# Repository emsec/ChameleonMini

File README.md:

Chameleon-Mini
==============
This is the official repository of ChameleonMini, a freely programmable, portable tool for NFC security analysis that can emulate and clone contactless cards, read RFID tags and sniff/log RF data. Thanks to over 1700 backers from our [Kickstarter project](https://www.kickstarter.com/projects/1980078555/chameleonmini-a-versatile-nfc-card-emulator-and-mo), the current Revision G has been realized by Kasper & Oswald GmbH.

The ChameleonMini RevG is now also available via the Kasper & Oswald [Webshop](https://shop.kasper.it/). Thank you for supporting the project!

IMPORTANT: Third-party Clones
------------------
We are aware of various third-party ChameleonMini clones or modified variants that are available on the Internet. Warning: We have evidence that some of these devices are defective or suffer from reading problems et cetera. Please understand that we cannot give support for these non-official devices, as we have no schematics / layout or other information, nor do we know the manufacturers. In case of problems, please contact the manufacturers of your device directly.

Note to the manufacturers: Some of the third-party ChameleonMini are violating the ChameleonMini license, please obey the license (see LICENSE.txt)!

First Steps
-----------
To upgrade the firmware of your ChameleonMini, please visit the [Getting Started page](https://cdn.statically.io/gh/emsec/ChameleonMini/master/Doc/Doxygen/html/Page_GettingStarted.html) from the [doxygen documentation](https://cdn.statically.io/gh/emsec/ChameleonMini/master/Doc/Doxygen/html/index.html).

Supported Cards and Codecs
--------------------------
See [here](https://github.com/emsec/ChameleonMini/wiki/Supported-Cards-and--Codecs). The linked wiki page also includes notes on DESFire emulation and certain cases of application specific emulation (Gallagher).

Questions
---------
If you have any questions, please visit the [Issues page](https://github.com/emsec/ChameleonMini/issues) and ask your questions there so everyone benefits from the answer.

**Please note that we cannot give any support if you have issues with the RevE-rebooted hardware or any GUI. Please use this issues page only for problems with the RevG hardware as distributed by Kasper & Oswald and for problems with the firmware from this page.** 

External Contributions
----------------------
We appreciate every contribution to the project. Have a look at the [External Contributions page](https://github.com/emsec/ChameleonMini/wiki/External-Contributions).

Repository Structure
--------------------
The code repository contains
* Doc: A doxygen documentation
* Drivers: Chameleon drivers for Windows and Linux
* Dumps: Dumps of different smartcards
* Hardware: The layout and schematics of the PCB
* Firmware: The complete firmware including a modified Atmel DFU bootloader and LUFA
* Software: Contains a python tool for an easy configuration (and more) of the ChameleonMini, Note that this is currently under construction
* RevE: Contains the whole contents of the discontinued RevE repository.
* RevE-light: Contains our development files for the RevE-light - **WARNING:** currently not supported / not functional

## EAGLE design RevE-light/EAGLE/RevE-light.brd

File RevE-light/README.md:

Chameleon-Mini RevE-light
==============

**WARNING:** The files in this folder are our current development version. *The hardware and software is not functional yet* - so do not use it. We will not answer any support inquiry regarding this version at the moment.

Structure
--------------------
This part of the code repository contains

* Hardware: The layout and schematics of the RevE-light - *NOT FUNCTIONAL*
* Firmware: The RevE-light firmware - *NOT FUNCTIONAL*

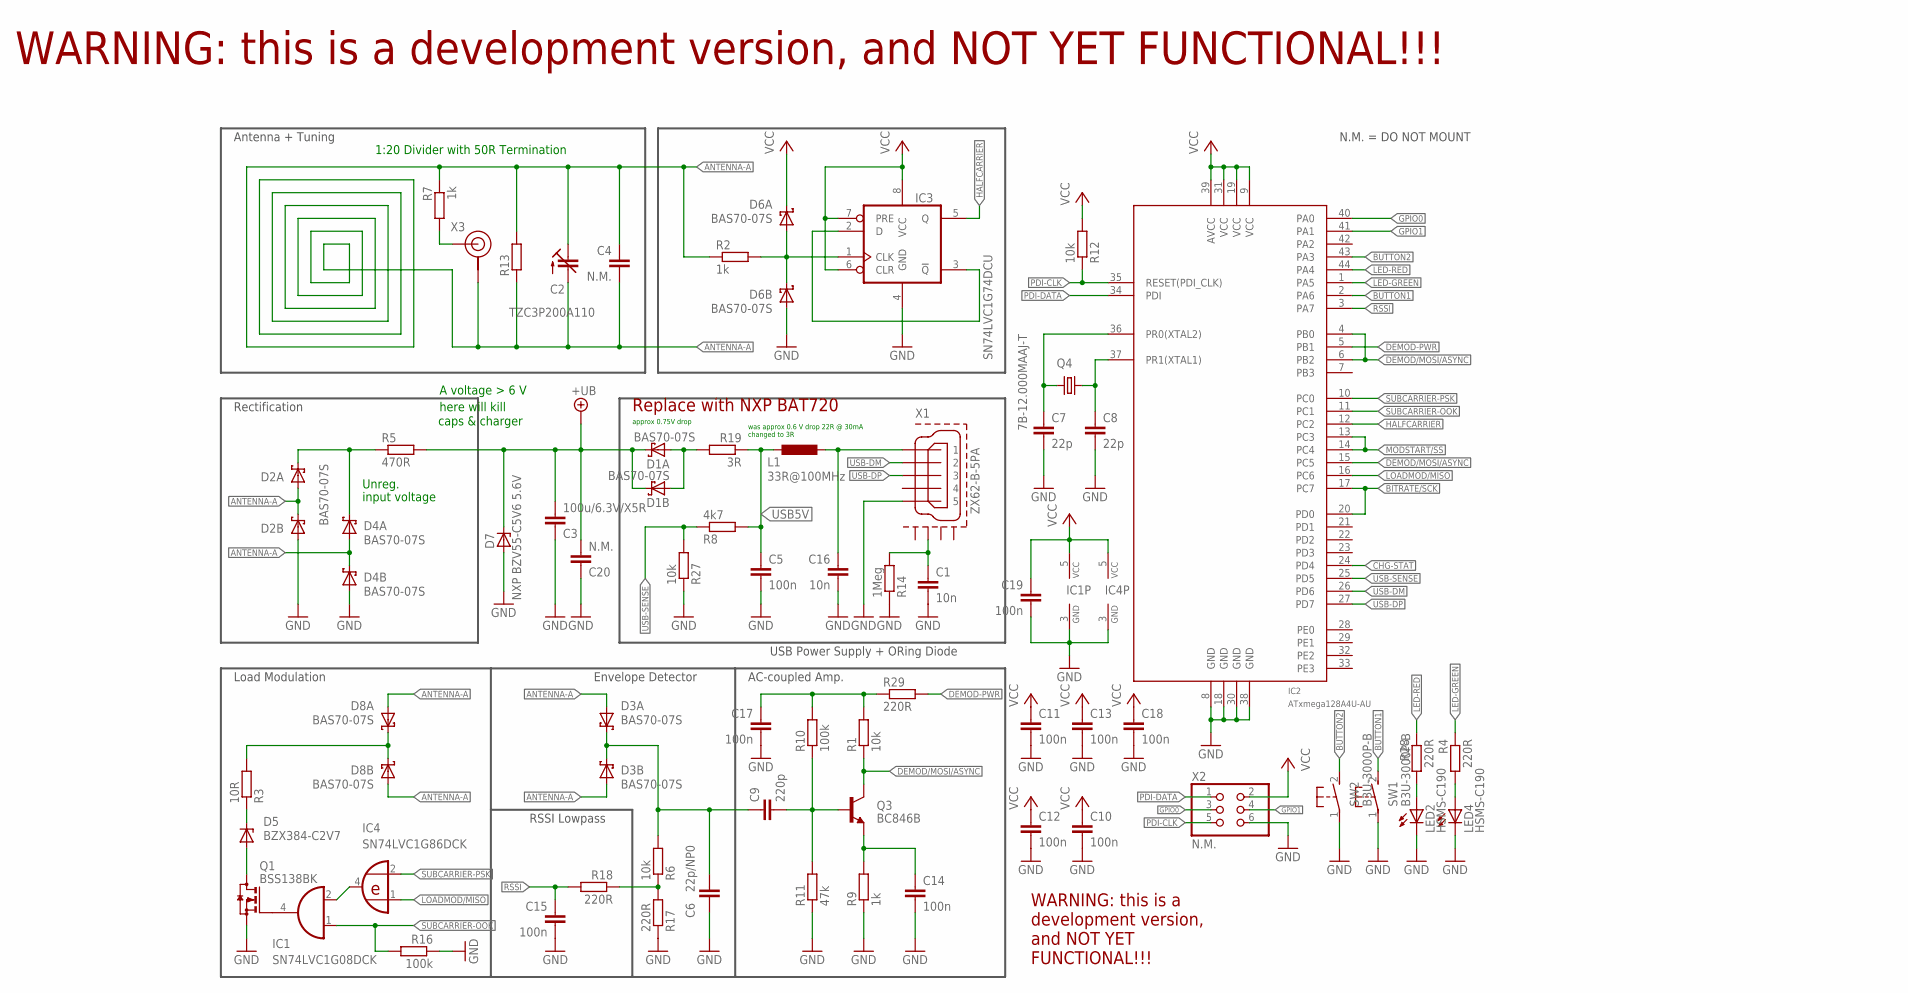
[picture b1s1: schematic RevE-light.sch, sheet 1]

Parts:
C1, C16: 10n; C1206K
C2: TZC3P200A110; TZC3P
C3: 100u/6.3V/X5R; C1206K
C4: N.M.; C1206
C5: 100n; C1206K
C6: 22p/NP0; C0603K
C7, C8: 22p; C0603K
C9: 220p; C0603K
C10, C11, C12, C13, C14, C15, C17, C18, C19: 100n; C0603K
C20: N.M.; C1206K
D1, D2, D3, D4, D6, D8: BAS70-07S; SOT363_PHILIPS
D5: BZX384-C2V7; SOD323
D7: NXP BZV55-C5V6 5.6V; SOD80C
IC1: SN74LVC1G08DCK; SC70-5
IC2: ATxmega128A4U-AU; TQFP44
IC3: SN74LVC1G74DCU; VSSOP8
IC4: SN74LVC1G86DCK; SC70-5
L1: 33R@100MHz; L2012C
LED2, LED4: HSMS-C190; CHIPLED_0603
Q1: BSS138BK; SOT23
Q3: BC846B; SOT23
Q4: 7B-12.000MAAJ-T; 5MMX3.2MM
R1, R6, R12, R27: 10k; R0603
R2, R9: 1k; R0603
R3: 10R; R0603
R4, R17, R18, R28, R29: 220R; R0603
R5: 470R; R1206
R7: 1k; R1206
R8: 4k7; R0603
R10, R16: 100k; R0603
R11: 47k; R0603
R13: R-EU_M1206; M1206
R14: 1Meg; M0805
R19: 3R; M0805
SW1, SW2: B3U-3000P-B
X1: ZX62-B-5PA; ZX62-B-5PA-LONG
X2: N.M.; PINHD-2X3-2.54-EDGE
X3: U.FL-R-SMT

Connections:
+UB: C3.2, C20.2, D1.3 (C), D1.6 (C), D7.C, R5.2; also elsewhere on the board
ANTENNA-A: C2.1 (A), C2.2 (E), C4.1, C4.2, D2.1 (A), D2.3 (C), D3.1 (A), D3.4 (A), D4.1 (A), D4.3 (C), D8.1 (A), D8.4 (A), R2.1, R7.1, R13.1, R13.2, X3.GND2 (GND)
BITRATE/SCK: IC2.17 (PC7), IC2.20 (PD0)
BUTTON1: IC2.2 (PA6), SW1.2 (S)
BUTTON2: IC2.43 (PA3), SW2.2 (S)
CHG-STAT: IC2.24 (PD4); also elsewhere on the board
DEMOD-PWR: IC2.5 (PB1), R29.2
DEMOD/MOSI/ASYNC: IC2.4 (PB0), IC2.6 (PB2), IC2.15 (PC5), Q3.3 (C), R1.1
GND: C1.2, C3.1, C5.2, C6.2, C7.2, C8.2, C10.2, C11.2, C12.2, C13.2, C14.2, C15.2, C16.2, C17.2, C18.2, C19.2, C20.1, D2.4 (A), D4.4 (A), D6.4 (A), D7.A, IC1.3 (GND), IC2.8 (GND), IC2.18 (GND), IC2.30 (GND), IC2.38 (GND), IC3.4 (GND), IC4.3 (GND), LED2.C, LED4.C, Q1.2 (S), R9.1, R11.1, R14.1, R16.1, R17.1, R27.1, SW1.1, SW2.1, X1.5, X2.6; also elsewhere on the board
GPIO0: IC2.40 (PA0), X2.3
GPIO1: IC2.41 (PA1), X2.4
HALFCARRIER: IC2.12 (PC2), IC3.5 (Q)
LED-GREEN: IC2.1 (PA5), R4.1
LED-RED: IC2.44 (PA4), R28.1
LOADMOD/MISO: IC2.16 (PC6), IC4.1 (I0)
MOD-DEMOD: D8.3 (C), D8.6 (C), R3.2
MOD-DEMOD1: C6.1, C9.1, D3.3 (C), D3.6 (C), R6.2
MODSTART/SS: IC2.13 (PC3), IC2.14 (PC4)
unnamed: C14.1, Q3.2 (E), R9.2
unnamed: D5.2 (A), Q1.3 (D)
unnamed: IC3.2 (D), IC3.3 (!Q)
unnamed: C7.1, IC2.36 (PR0(XTAL2)), Q4.3 (2)
unnamed: R6.1, R17.2, R18.1
unnamed: C16.1, L1.1, X1.1
unnamed: C8.1, IC2.37 (PR1(XTAL1)), Q4.1
unnamed: LED2.A, R28.2
unnamed: D2.6 (C), D4.6 (C), R5.1
unnamed: IC1.2 (I1), IC4.4 (O)
unnamed: D5.1 (C), R3.1
unnamed: LED4.A, R4.2
unnamed: IC1.4 (O), Q1.1 (G)
unnamed: R7.2, X3.SIG
unnamed: C9.2, Q3.1 (B), R10.1, R11.2
unnamed: C1.1, R14.2, X1.P$2 (GND2)
unnamed: D1.1 (A), D1.4 (A), R19.2
unnamed: D6.1 (A), D6.3 (C), IC3.1 (CLK), R2.2
unnamed: C17.1, R1.2, R10.2, R29.1
PDI-CLK: IC2.35 (RESET(PDI_CLK)), R12.1, X2.5
PDI-DATA: IC2.34 (PDI), X2.1
RSSI: C15.1, IC2.3 (PA7), R18.2
SUBCARRIER-OOK: IC1.1 (I0), IC2.11 (PC1), R16.2
SUBCARRIER-PSK: IC2.10 (PC0), IC4.2 (I1)
USB5V: C5.1, L1.2, R8.2, R19.1
USB-DM: IC2.26 (PD6), X1.2
USB-DP: IC2.27 (PD7), X1.3
USB-SENSE: IC2.25 (PD5), R8.1, R27.2
VCC: C10.1, C11.1, C12.1, C13.1, C18.1, C19.1, D6.6 (C), IC1.5 (VCC), IC2.9 (VCC), IC2.19 (VCC), IC2.31 (VCC), IC2.39 (AVCC), IC3.6 (CLR), IC3.7 (PRE), IC3.8 (VCC), IC4.5 (VCC), R12.2, X2.2; also elsewhere on the board

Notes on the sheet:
1:20 Divider with 50R Termination
Envelope Detector
RSSI Lowpass
AC-coupled Amp.
Load Modulation
Rectification
USB Power Supply + ORing Diode
Antenna + Tuning
WARNING: this is a development version, and NOT YET FUNCTIONAL!!!
N.M. = DO NOT MOUNT
Unreg.
input voltage
A voltage > 6 V
here will kill
caps & charger
was approx 0.6 V drop 22R @ 30mA changed to 3R
approx 0.75V drop
Replace with NXP BAT720
WARNING: this is a development version, and NOT YET FUNCTIONAL!!!

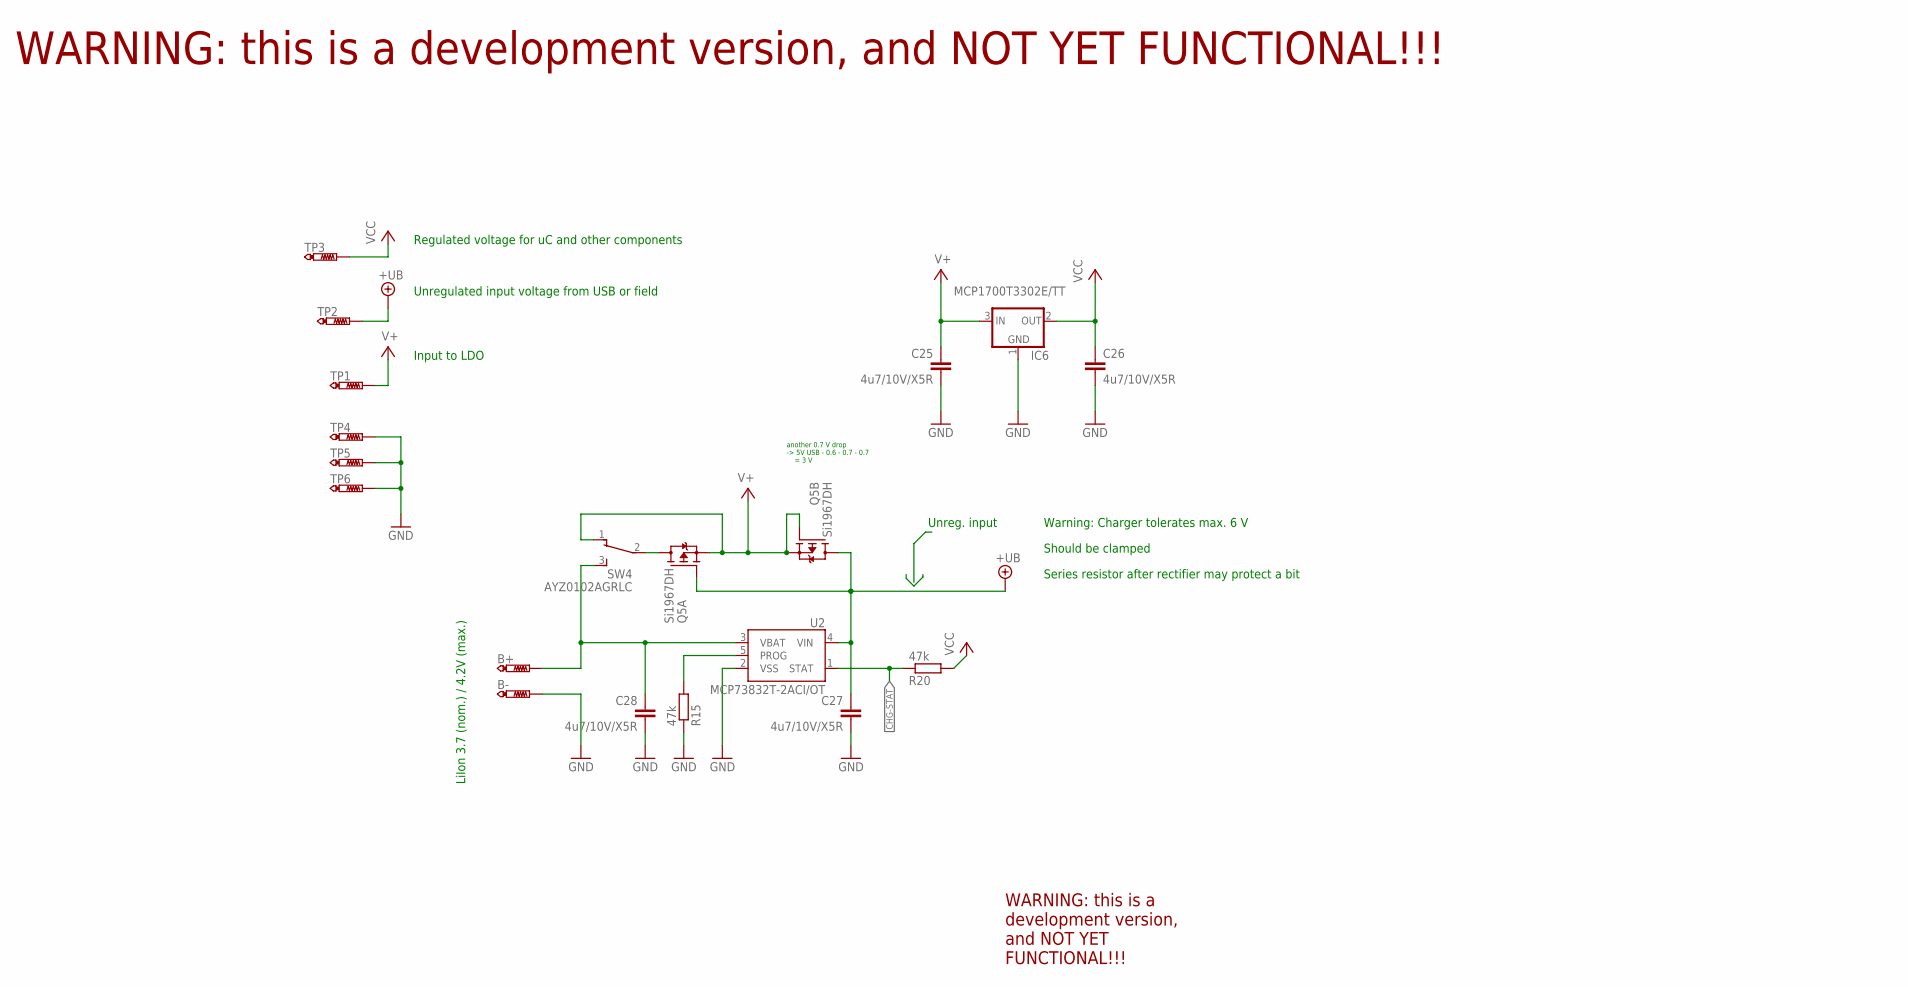
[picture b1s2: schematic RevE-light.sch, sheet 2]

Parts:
B+: PTR1TP18SQ; TP18SQ
B-: PTR1TP18SQ; TP18SQ
C25, C26, C27, C28: 4u7/10V/X5R; C0603K
IC6: MCP1700T3302E/TT; SOT23
Q5: Si1967DH; SOT363
R15, R20: 47k; R0603
SW4: AYZ0102AGRLC
TP1, TP2, TP3, TP4, TP5, TP6: PTR1TP07R; TP07R
U2: MCP73832T-2ACI/OT; SOT23-5

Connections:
+UB: C27.1, Q5.2 (G), Q5.3 (D), TP2.TP, U2.4 (VIN); also elsewhere on the board
CHG-STAT: R20.1, U2.1 (STAT); also elsewhere on the board
GND: B-.TP, C25.2, C26.2, C27.2, C28.2, IC6.1 (GND), R15.1, TP4.TP, TP5.TP, TP6.TP, U2.2 (VSS); also elsewhere on the board
unnamed: B+.TP, C28.1, SW4.3 (S), U2.3 (VBAT)
unnamed: R15.2, U2.5 (PROG)
unnamed: Q5.6 (D), SW4.2
V+: C25.1, IC6.3 (IN), Q5.1 (S), Q5.4 (S), Q5.5 (G), SW4.1 (O), TP1.TP
VCC: C26.1, IC6.2 (OUT), R20.2, TP3.TP; also elsewhere on the board

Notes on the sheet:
Regulated voltage for uC and other components
Unregulated input voltage from USB or field
Unreg. input
LiIon 3.7 (nom.) / 4.2V (max.)
Input to LDO
Warning: Charger tolerates max. 6 V
Should be clamped
Series resistor after rectifier may protect a bit
another 0.7 V drop -> 5V USB - 0.6 - 0.7 - 0.7 = 3 V
WARNING: this is a development version, and NOT YET FUNCTIONAL!!!
WARNING: this is a development version, and NOT YET FUNCTIONAL!!!

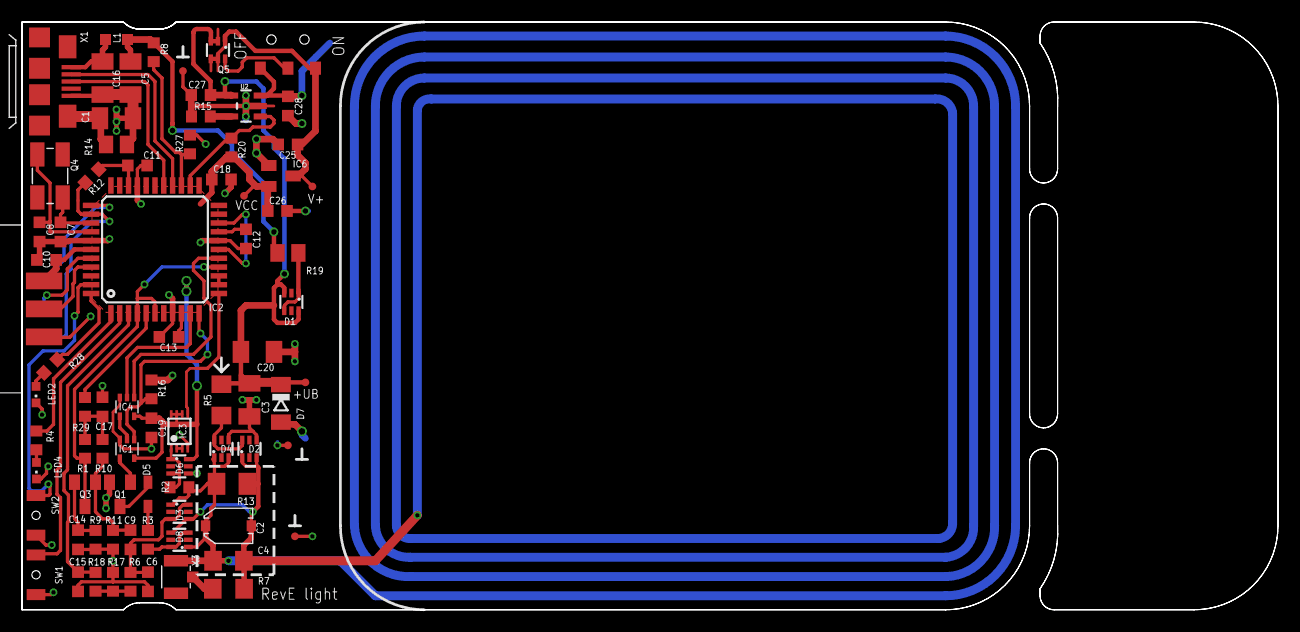
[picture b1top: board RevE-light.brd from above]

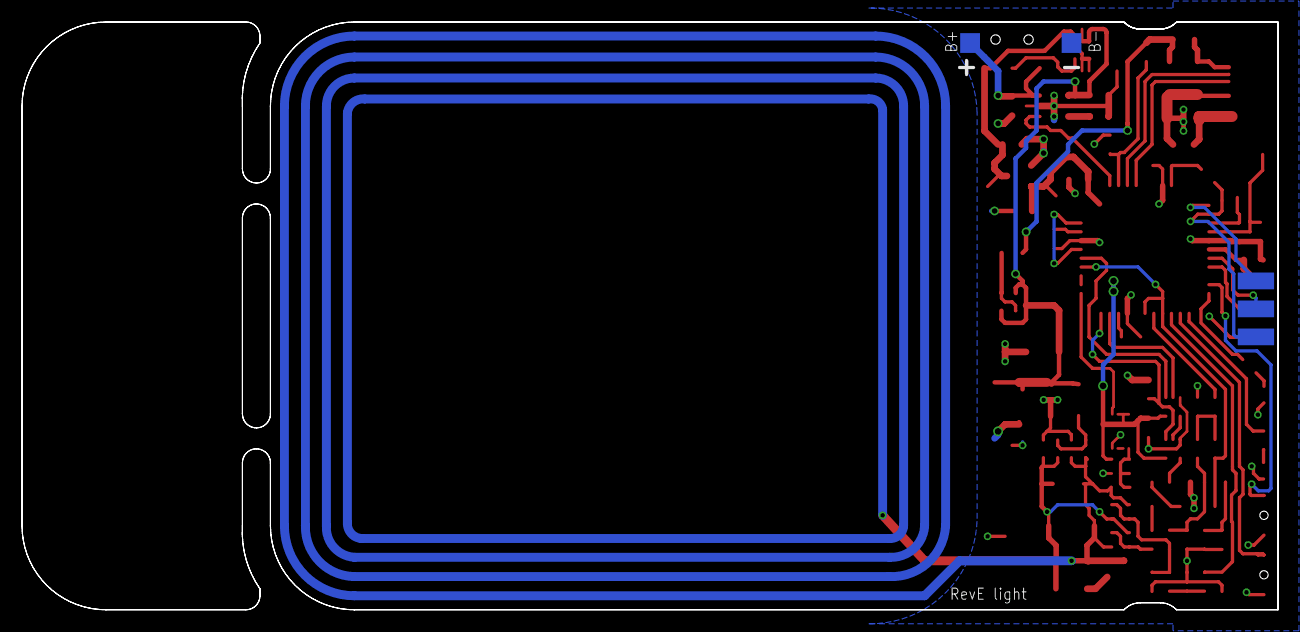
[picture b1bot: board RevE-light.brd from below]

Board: 2 copper layers, 114.0 x 53.3 mm, 82 parts (2 on the bottom side), 51 nets.

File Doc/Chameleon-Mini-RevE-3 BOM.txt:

Stückliste exportiert aus /home/neo/Downloads/ChameleonMini-master/ChameleonMini-masterneo/EAGLE/Chameleon-Mini-RevE-3.sch am 12.02.14 13:28

Qty Value                   Device                  Package              Parts                                       Description                                 
1                           PINHD-2X3-2.54-EDGE     PINHD-2X3-2.54-EDGE  X2                                                                                      
2   100k                    R-EU_R0603              R0603                R10, R16                                    RESISTOR, European symbol                   
9   100n                    C-EUC0603K              C0603K               C10, C11, C12, C13, C14, C15, C17, C18, C19 CAPACITOR, European symbol                  
1   100n                    C-EUC1206K              C1206K               C5                                          CAPACITOR, European symbol                  
1   10R                     R-EU_R0603              R0603                R3                                          RESISTOR, European symbol                   
4   10k                     R-EU_R0603              R0603                R1, R6, R12, R27                            RESISTOR, European symbol                   
2   10n                     C-EUC1206K              C1206K               C1, C16                                     CAPACITOR, European symbol                  
1   10u/6.3V/X5R            C-EUC1206K              C1206K               C3                                          CAPACITOR, European symbol                  
1   120k                    R-EU_R0603              R0603                R15                                         RESISTOR, European symbol                   
1   12MHz                   TXC7B                   5MMX3.2MM            Q4                                                                                      
1   1Meg                    R-EU_R1206              R1206                R14                                         RESISTOR, European symbol                   
2   1k                      R-EU_R0603              R0603                R2, R9                                      RESISTOR, European symbol                   
1   1k                      R-EU_R1206              R1206                R7                                          RESISTOR, European symbol                   
1   200k                    R-EU_R0603              R0603                R13                                         RESISTOR, European symbol                   
5   220R                    R-EU_R0603              R0603                R4, R17, R18, R28, R29                      RESISTOR, European symbol                   
1   220p                    C-EUC0603K              C0603K               C9                                          CAPACITOR, European symbol                  
1   22R                     R-EU_R1206              R1206                R19                                         RESISTOR, European symbol                   
2   22p                     C-EUC0603K              C0603K               C7, C8                                      CAPACITOR, European symbol                  
1   22p/NP0                 C-EUC0603K              C0603K               C6                                          CAPACITOR, European symbol                  
1   33R@100MHz              L-EUL2012C              L2012C               L1                                          INDUCTOR, European symbol                   
1   470R                    R-EU_R1206              R1206                R5                                          RESISTOR, European symbol                   
1   47k                     R-EU_R0603              R0603                R11                                         RESISTOR, European symbol                   
1   4k7                     R-EU_R0603              R0603                R8                                          RESISTOR, European symbol                   
1   AT45DB081E-SSHN-B       AT45DB041B              SO08                 IC10                                                                                    
1   ATxmega32A4U-AU         ATXMEGA_A4-A            TQFP44               IC2                                                                                     
6   BAS70-07S               BAS70-07S               SOT363_PHILIPS       D1, D2, D3, D4, D6, D8                      Silicon Schottky Diodes                     
1   BC846B                  BC846BSMD               SOT23                Q3                                          NPN Transistor                              
1   BSS138BK                BSS123                  SOT23                Q1                                          N-CHANNEL MOS FET                           
1   BZX384-C2V7             BZX384                  SOD323               D5                                                                                      
1   GREEN                   LEDCHIPLED_0805         CHIPLED_0805         LED4                                        LED                                         
1   N.M.                    C-EUC1206               C1206                C4                                          CAPACITOR, European symbol                  
1   RED                     LEDCHIPLED_0805         CHIPLED_0805         LED2                                        LED                                         
1   SN74LVC1G08DCK          74LVC1G08DCK            SC70-5               IC1                                         2-input AND gate                            
1   SN74LVC1G74DCU          74LVC1G74DC             VSSOP8               IC3                                                                                     
1   SN74LVC1G86DCK          74AHC1G86DCK            SC70-5               IC4                                         2-input EXCLUSIV-OR gate                    
1   SWITCH-MOMENTARY-2SMD-3 SWITCH-MOMENTARY-2SMD-3 TACTILE_SWITCH_SMD-3 S1                                          Various NO switches- pushbuttons, reed, etc 
1   TLVH431(A)IDBZR         TLVH431-SOT23           SOT23                VR1                                                                                     
1   TZC3P200A110            TZC3P                   TZC3P                C2                                                                                      
1   U.FL-R-SMT              U.FL-R-SMT              U.FL-R-SMT           X3                                                                                      
1   ZX62-B-5PA              ZX62-B-5PA-LONG         ZX62-B-5PA-LONG      X1

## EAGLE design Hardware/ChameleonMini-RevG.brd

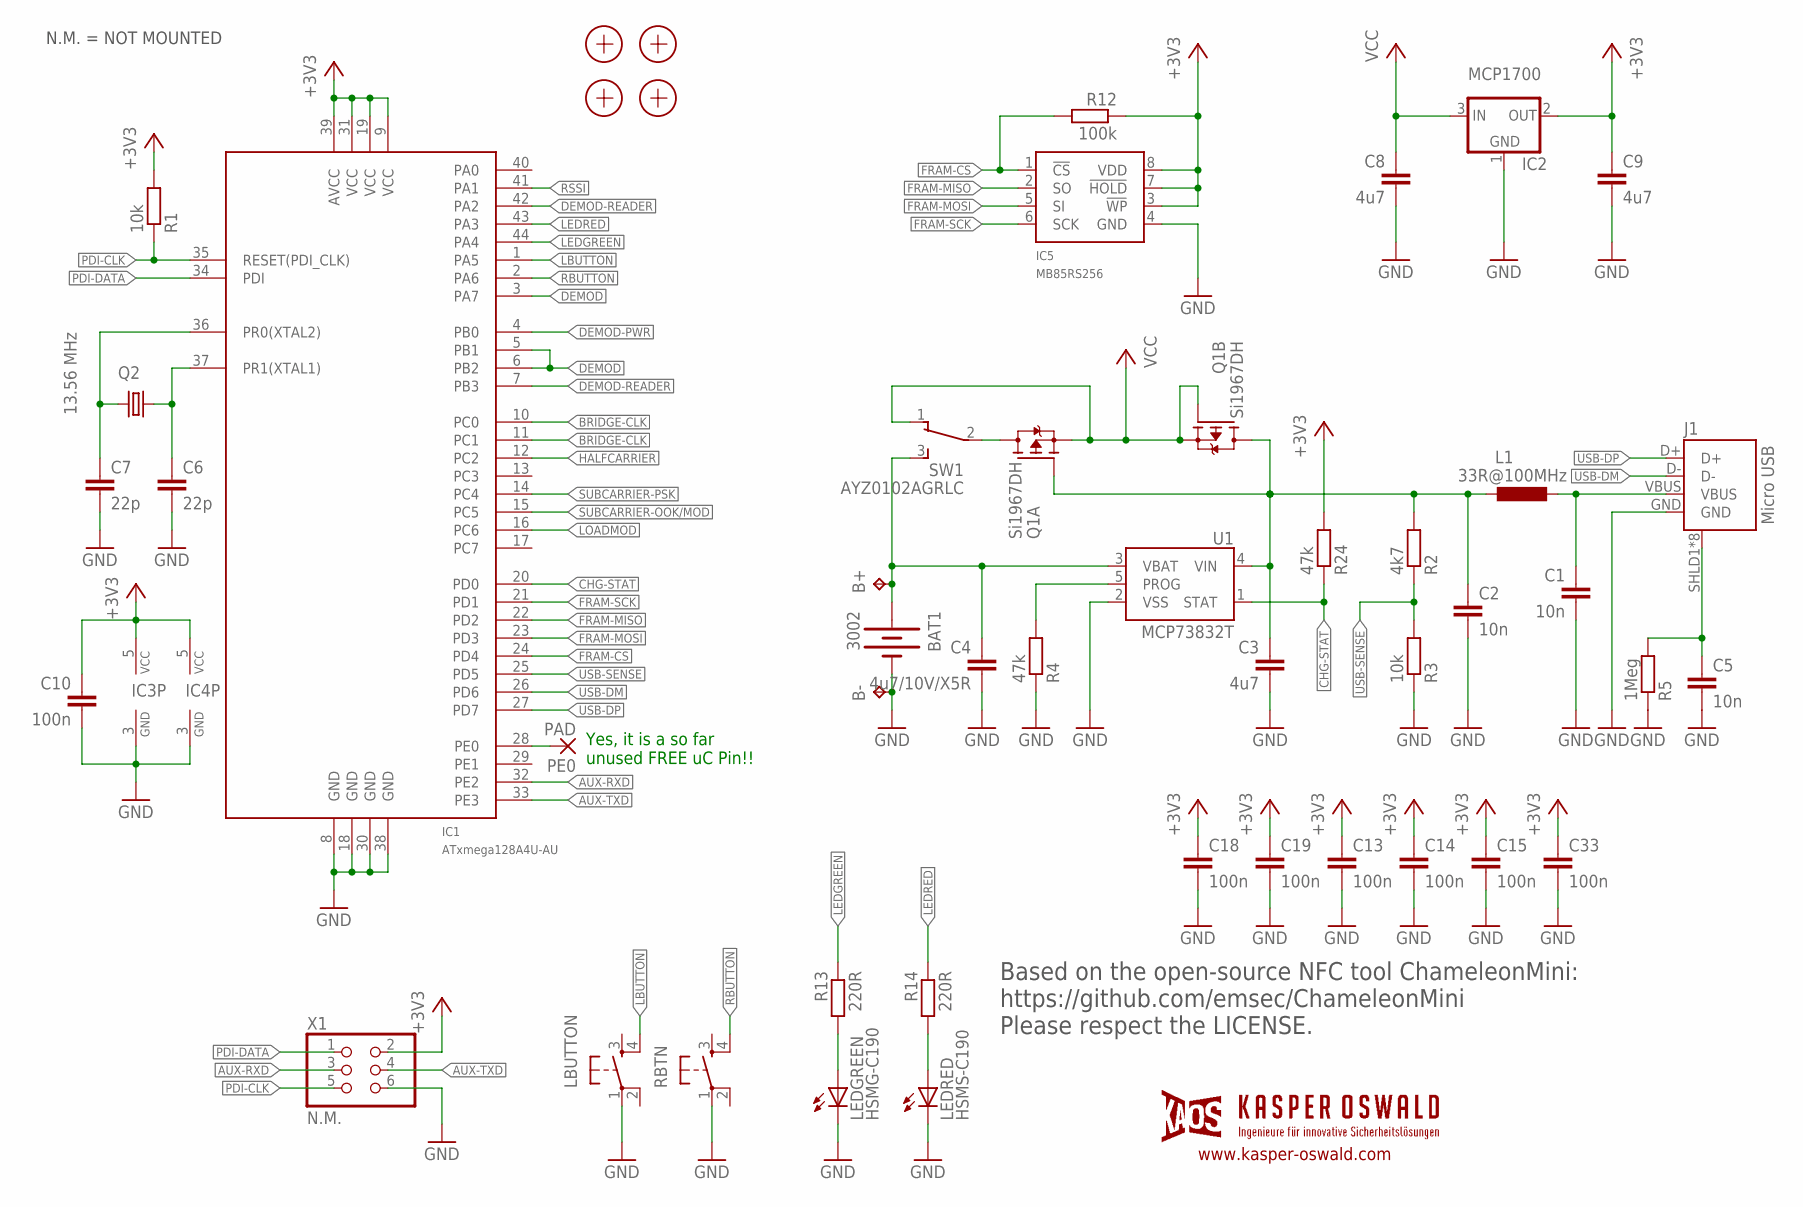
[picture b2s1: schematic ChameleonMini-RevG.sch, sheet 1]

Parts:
B+: TPTP18SQ; TP18SQ
B-: TPTP18SQ; TP18SQ
BAT1: 3002; BATTCON_20MM
C1, C2: 10n; C1206K
C3, C8, C9: 4u7; C0603K
C4: 4u7/10V/X5R; C0603K
C5: 10n; C0603K
C6, C7: 22p; C0603K
C10, C13, C14, C15, C18, C19, C33: 100n; C0603K
IC1: ATxmega128A4U-AU; TQFP44
IC2: MCP1700; SOT23
IC3: 7408; SC70-5
IC4: 7486; SC70-5
IC5: MB85RS256; SO-08
J1: Micro USB; USB-MICROB-10118194
L1: 33R@100MHz; L2012C
LBUTTON: SWITCH_SPST_4_PINSQUARE; TACTILE-SWITCH-SMD
LEDGREEN: HSMG-C190; CHIPLED-0603
LEDRED: HSMS-C190; CHIPLED-0603
PE0: PAD; SMD1,27-2,54
Q1: Si1967DH; SOT363
Q2: 13.56 MHz; 5MMX3.2MM
R1, R3: 10k; R0603
R2: 4k7; R0603
R4, R24: 47k; R0603
R5: 1Meg; R0603
R12: 100k; R0603
R13, R14: 220R; R0603
RBTN: SWITCH_SPST_4_PINSQUARE; TACTILE-SWITCH-SMD
SW1: AYZ0102AGRLC
U1: MCP73832T; SOT23-5
X1: N.M.; PINHD-2X3-2.54-EDGE
X2, X4, X5, X6: PASSER-07; PASSER_07MM

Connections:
!BRIDGE-CLK: IC1.10 (PC0); also elsewhere on the board
+3V3: C9.1, C10.1, C13.1, C14.1, C15.1, C18.1, C19.1, C33.1, IC1.9 (VCC), IC1.19 (VCC), IC1.31 (VCC), IC1.39 (AVCC), IC2.2 (OUT), IC3.5 (VCC), IC4.5 (VCC), IC5.3 (!WP), IC5.7 (!HOLD), IC5.8 (VDD), R1.2, R12.1, R24.2, X1.2; also elsewhere on the board
AUX-RXD: IC1.32 (PE2), X1.3
AUX-TXD: IC1.33 (PE3), X1.4
BRIDGE-CLK: IC1.11 (PC1); also elsewhere on the board
CHG-STAT: IC1.20 (PD0), R24.1, U1.1 (STAT)
DEMOD: IC1.3 (PA7), IC1.5 (PB1), IC1.6 (PB2); also elsewhere on the board
DEMOD-PWR: IC1.4 (PB0); also elsewhere on the board
DEMOD-READER: IC1.7 (PB3), IC1.42 (PA2); also elsewhere on the board
FRAM-CS: IC1.24 (PD4), IC5.1 (!CS), R12.2
FRAM-MISO: IC1.22 (PD2), IC5.2 (SO)
FRAM-MOSI: IC1.23 (PD3), IC5.5 (SI)
FRAM-SCK: IC1.21 (PD1), IC5.6 (SCK)
GND: B-.TP, BAT1.-, C1.2, C2.2, C3.2, C4.2, C5.2, C6.2, C7.2, C8.2, C9.2, C10.2, C13.2, C14.2, C15.2, C18.2, C19.2, C33.2, IC1.8 (GND), IC1.18 (GND), IC1.30 (GND), IC1.38 (GND), IC2.1 (GND), IC3.3 (GND), IC4.3 (GND), IC5.4 (GND), J1.GND, LBUTTON.1, LEDGREEN.C, LEDRED.C, R3.1, R4.1, R5.1, RBTN.1, U1.2 (VSS), X1.6; also elsewhere on the board
HALFCARRIER: IC1.12 (PC2); also elsewhere on the board
LBUTTON: IC1.1 (PA5), LBUTTON.4
LEDGREEN: IC1.44 (PA4), R13.1
LEDRED: IC1.43 (PA3), R14.1
LOADMOD: IC1.16 (PC6); also elsewhere on the board
unnamed: C7.1, IC1.36 (PR0(XTAL2)), Q2.3 (2)
unnamed: C1.1, J1.VBUS, L1.1
unnamed: C6.1, IC1.37 (PR1(XTAL1)), Q2.1
unnamed: LEDGREEN.A, R13.2
unnamed: LEDRED.A, R14.2
unnamed: Q1.6 (D), SW1.2
unnamed: C2.1, C3.1, L1.2, Q1.2 (G), Q1.3 (D), R2.2, U1.4 (VIN)
unnamed: IC1.28 (PE0), PE0.1
unnamed: R4.2, U1.5 (PROG)
unnamed: B+.TP, BAT1.+2 (+), C4.1, SW1.3 (S), U1.3 (VBAT)
unnamed: C5.1, J1.SHLD1 (SHIELD), J1.SHLD2 (SHIELD), J1.SHLD3 (SHIELD), J1.SHLD4 (SHIELD), J1.SHLD5 (SHIELD), J1.SHLD6 (SHIELD), J1.SHLD7 (SHIELD), J1.SHLD8 (SHIELD), R5.2
PDI-CLK: IC1.35 (RESET(PDI_CLK)), R1.1, X1.5
PDI-DATA: IC1.34 (PDI), X1.1
RBUTTON: IC1.2 (PA6), RBTN.4
RSSI: IC1.41 (PA1); also elsewhere on the board
SUBCARRIER-OOK/MOD: IC1.15 (PC5); also elsewhere on the board
SUBCARRIER-PSK: IC1.14 (PC4); also elsewhere on the board
USB-DM: IC1.26 (PD6), J1.D-
USB-DP: IC1.27 (PD7), J1.D+
USB-SENSE: IC1.25 (PD5), R2.1, R3.2
VCC: C8.1, IC2.3 (IN), Q1.1 (S), Q1.4 (S), Q1.5 (G), SW1.1 (O)

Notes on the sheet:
Based on the open-source NFC tool ChameleonMini: https://github.com/emsec/ChameleonMini Please respect the LICENSE.
N.M. = NOT MOUNTED
Yes, it is a so far unused FREE uC Pin!!
www.kasper-oswald.com

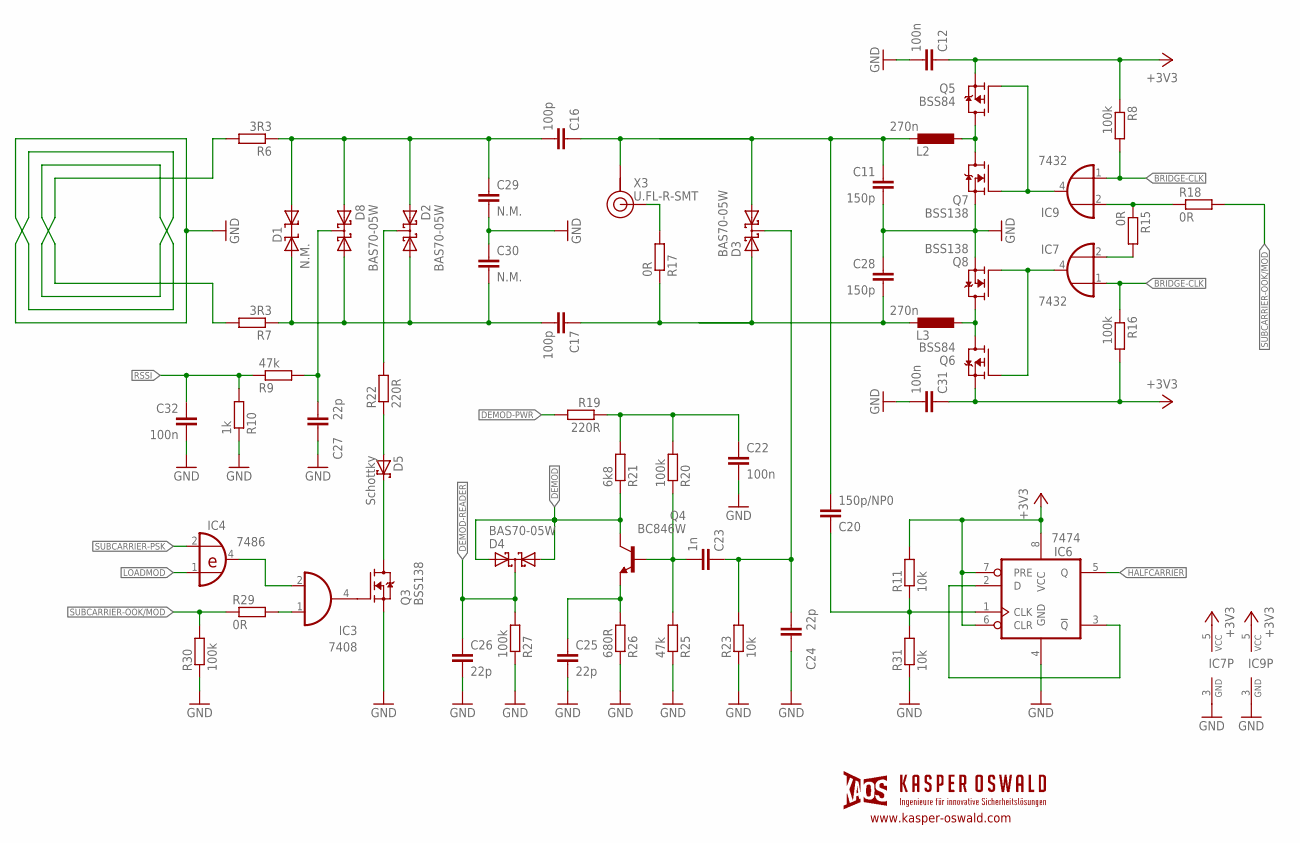
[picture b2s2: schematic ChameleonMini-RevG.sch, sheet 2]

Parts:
C11, C28: 150p; C0603K
C12, C22, C31, C32: 100n; C0603K
C16, C17: 100p; C0603K
C20: 150p/NP0; C0603K
C23: 1n; C0603K
C24, C25, C26, C27: 22p; C0603K
C29, C30: N.M.; C0603K
D1: N.M.; DO214AC
D2, D3, D4, D8: BAS70-05W; SOT323
D5: Schottky; SOD323(F)
IC3: 7408; SC70-5
IC4: 7486; SC70-5
IC6: 7474; VSSOP8
IC7, IC9: 7432; SC70-5
L2, L3: 270n; L2012C
Q3, Q7, Q8: BSS138; SOT323
Q4: BC846W; SOT323
Q5, Q6: BSS84; SOT323
R6, R7: 3R3; R0603
R8, R16, R20, R27, R30: 100k; R0603
R9, R25: 47k; R0603
R10: 1k; R0603
R11, R23, R31: 10k; R0603
R15, R17, R18, R29: 0R; R0603
R19, R22: 220R; R0603
R21: 6k8; R0603
R26: 680R; R0603
X3: U.FL-R-SMT

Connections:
!BRIDGE-CLK: IC7.1 (I0), R16.1; also elsewhere on the board
+3V3: C12.1, C31.1, IC6.6 (CLR), IC6.7 (PRE), IC6.8 (VCC), IC7.5 (VCC), IC9.5 (VCC), Q5.2 (S), Q6.2 (S), R8.1, R11.2, R16.2; also elsewhere on the board
ANTENNA-A: C11.1, C16.1, C20.2, D3.2 (A2), L2.2, X3.GND1 (GND)
ANTENNA-B: C17.1, C28.2, D3.1 (A1), L3.2, R17.1
BRIDGE-1: IC9.4 (O), Q5.1 (G), Q7.1 (G)
BRIDGE-2: IC7.4 (O), Q6.1 (G), Q8.1 (G)
BRIDGE-CLK: IC9.1 (I0), R8.2; also elsewhere on the board
DEMOD: D4.1 (A1), D4.2 (A2), Q4.3 (C), R21.1; also elsewhere on the board
DEMOD-PWR: R19.2; also elsewhere on the board
DEMOD-READER: C26.1, D4.3 (K), R27.2; also elsewhere on the board
GND: C11.2, C12.2, C22.2, C24.2, C25.2, C26.2, C27.2, C28.1, C29.2, C30.1, C31.2, C32.2, IC6.4 (GND), IC7.3 (GND), IC9.3 (GND), Q3.2 (S), Q7.2 (S), Q8.2 (S), R6.2, R7.2, R10.1, R23.1, R25.1, R26.1, R27.1, R30.1, R31.1; also elsewhere on the board
HALFCARRIER: IC6.5 (Q); also elsewhere on the board
LOADMOD: IC4.1 (I0); also elsewhere on the board
MOD-DEMOD: D2.3 (K), R22.2
MOD-DEMOD1: C23.1, C24.1, D3.3 (K), R23.2
unnamed: C25.1, Q4.2 (E), R26.2
unnamed: IC7.2 (I1), R15.2
unnamed: D5.1 (K), Q3.3 (D)
unnamed: IC6.2 (D), IC6.3 (!Q)
unnamed: C16.2, C29.1, D1.2, D2.1 (A1), D8.1 (A1), R6.1
unnamed: L2.1, Q5.3 (D), Q7.3 (D)
unnamed: IC3.2 (I1), IC4.4 (O)
unnamed: D5.2 (A), R22.1
unnamed: IC3.4 (O), Q3.1 (G)
unnamed: R17.2, X3.SIG
unnamed: L3.1, Q6.3 (D), Q8.3 (D)
unnamed: C17.2, C30.2, D1.1, D2.2 (A2), D8.2 (A2), R7.1
unnamed: C27.1, D8.3 (K), R9.2
unnamed: IC9.2 (I1), R15.1, R18.1
unnamed: C23.2, Q4.1 (B), R20.1, R25.2
unnamed: C20.1, IC6.1 (CLK), R11.1, R31.2
unnamed: IC3.1 (I0), R29.2
unnamed: C22.1, R19.1, R20.2, R21.2
RSSI: C32.1, R9.1, R10.2; also elsewhere on the board
SUBCARRIER-OOK/MOD: R18.2, R29.1, R30.2; also elsewhere on the board
SUBCARRIER-PSK: IC4.2 (I1); also elsewhere on the board

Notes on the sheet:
www.kasper-oswald.com

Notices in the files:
parts and their libraries:
SparkFun-Electromechanical: Licensing: Creative Commons ShareAlike 4.0 International - https://creativecommons.org/licenses/by-sa/4.0
